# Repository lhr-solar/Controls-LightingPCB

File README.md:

# Controls-LightingPCB

Purpose: This board controls all lightings effects activated by driver controls on the inside and outside of the car.

Dimensions: 73.9140 mm by 98.8060 mm

BOM: Located under Controls-LightingPCB\BOM

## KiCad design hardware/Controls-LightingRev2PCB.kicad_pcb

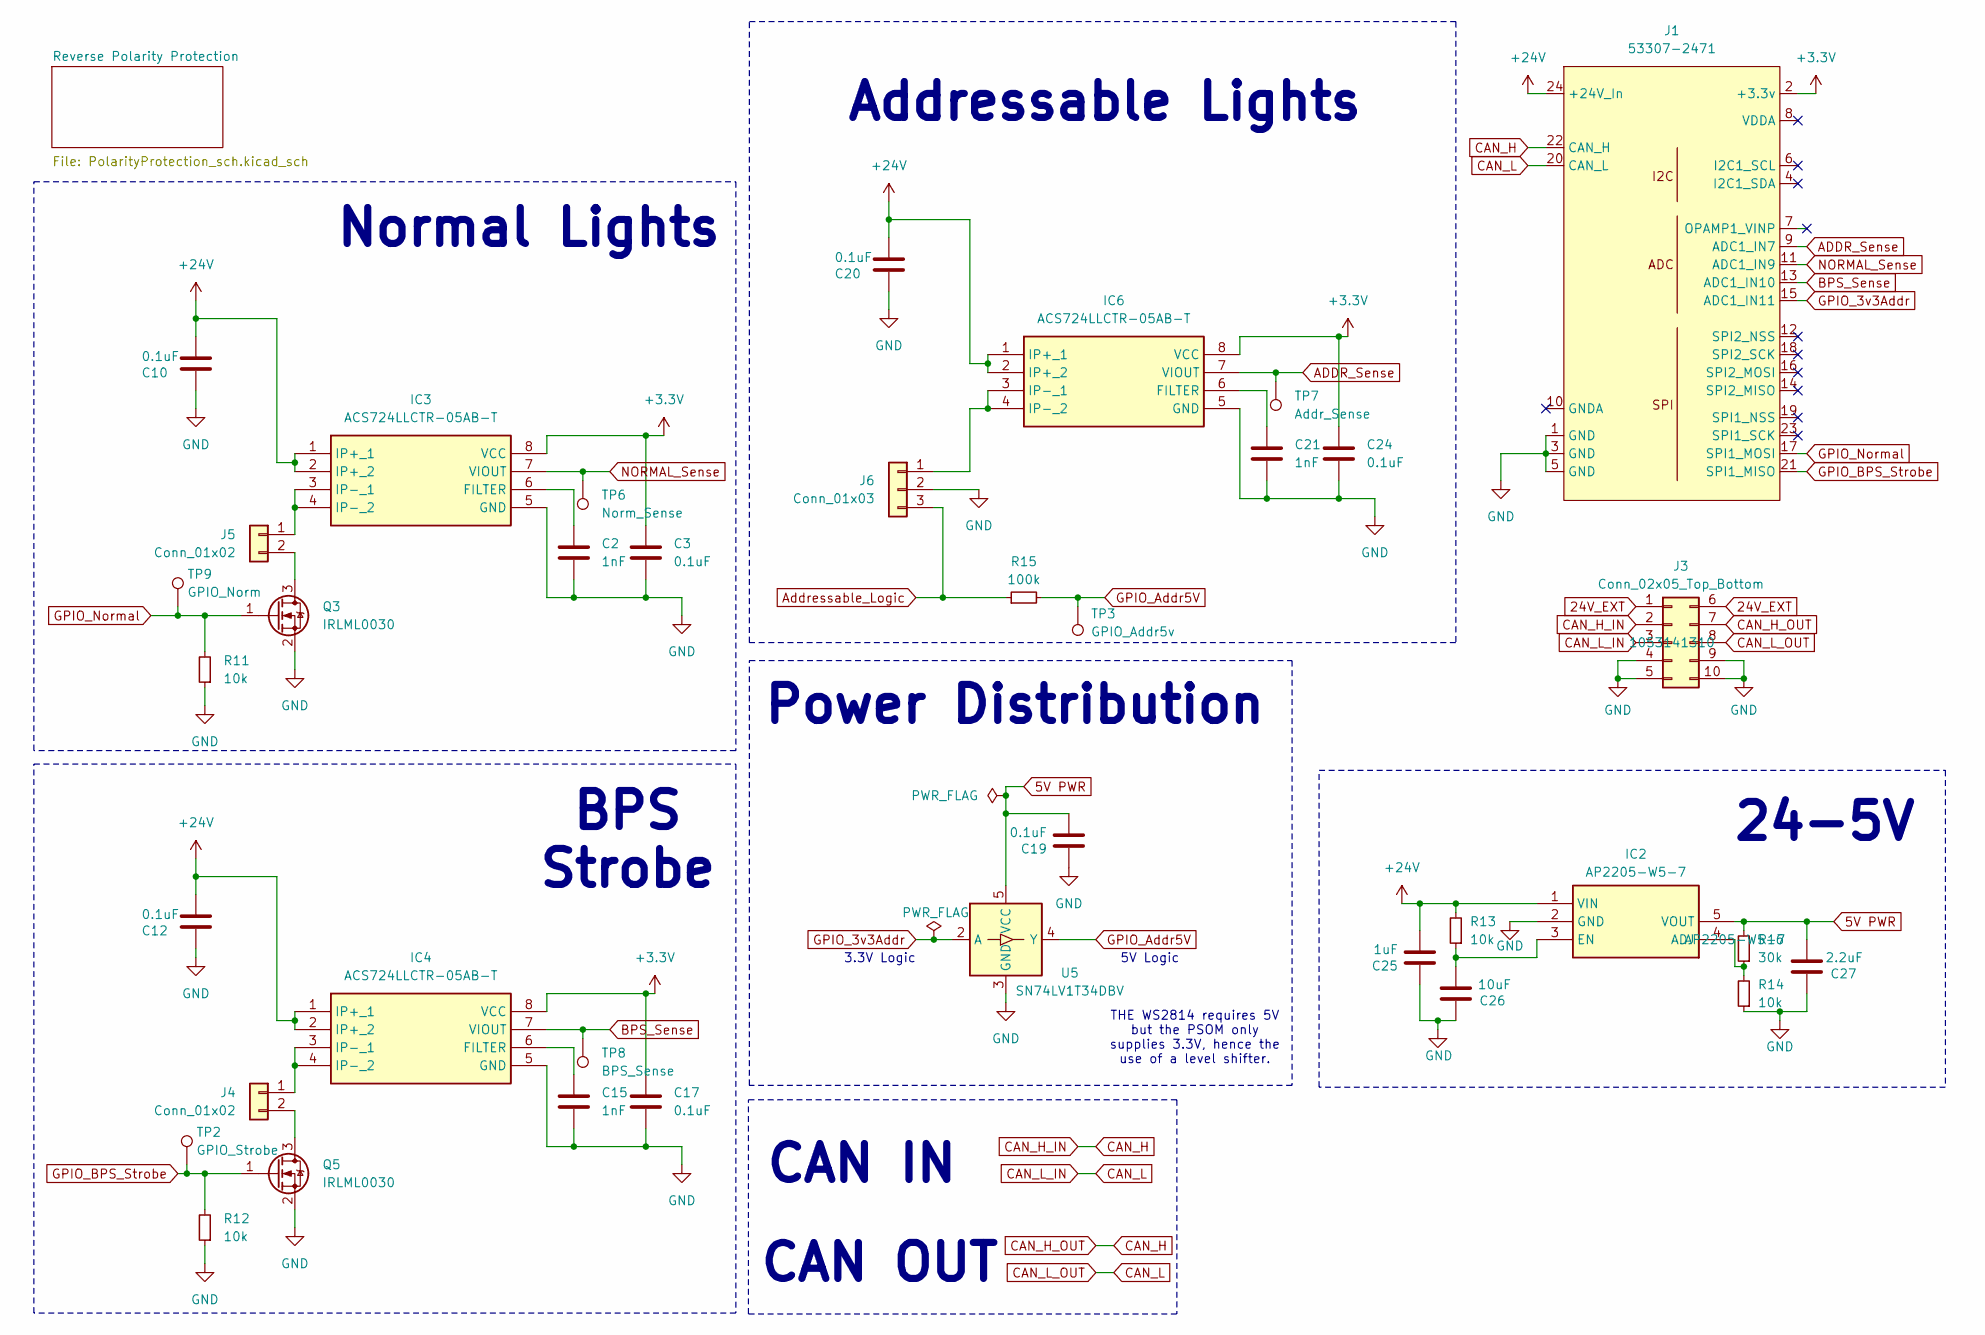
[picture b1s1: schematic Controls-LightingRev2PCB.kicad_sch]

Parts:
C2, C15, C21: 1nF; C_0603_1608Metric; LCSC P/N C1588
C3, C10, C12, C17, C19, C20, C24: 0.1uF; C_0603_1608Metric; LCSC P/N C14663
C25: 1uF; C_0603_1608Metric; LCSC P/N C15849
C26: 10uF; C_0805_2012Metric_Pad1.18x1.45mm_HandSolder; LCSC P/N C440198
C27: 2.2uF; C_0603_1608Metric; LCSC P/N C57895
IC2: AP2205-W5-7; AP2205W57; Mouser Part Number 621-AP2205-W5-7
IC3: ACS724LLCTR-05AB-T; SOIC127P600X175-8N; LCSC P/N C22392329
IC4: ACS724LLCTR-05AB-T; SOIC127P600X175-8N; Manufacturer_Part_Number ACS724LLCTR-05AB-T; LCSC P/N C22392329
IC6: ACS724LLCTR-05AB-T; SOIC127P600X175-8N; Mouser Part Number ACS724LLCTR-05AB-T
J1: 53307-2471; PeripheralSOM
J3: Conn_02x05_Top_Bottom; Molex_Nano-Fit_105314-xx10_2x05_P2.50mm_Horizontal
J4, J5: Conn_01x02; 105313-2102
J6: Conn_01x03; 105313-1103
Q3, Q5: IRLML0030; SOT-23; LCSC P/N C67272
R11, R12, R13, R14: 10k; R_0603_1608Metric; LCSC P/N C25804
R15: 100k; R_0603_1608Metric; LCSC P/N C25803
R16: 30k; R_0603_1608Metric; LCSC P/N C18681
TP2: GPIO_Strobe; TestPoint_Keystone_5005-5009_Compact
TP3: GPIO_Addr5v; TestPoint_Keystone_5005-5009_Compact
TP6: Norm_Sense; TestPoint_Keystone_5005-5009_Compact
TP7: Addr_Sense; TestPoint_Keystone_5005-5009_Compact
TP8: BPS_Sense; TestPoint_Keystone_5005-5009_Compact
TP9: GPIO_Norm; TestPoint_Keystone_5005-5009_Compact
U5: SN74LV1T34DBV; SOT-23-5; LCSC P/N C47117565

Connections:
5V PWR: C19.2, C27.2, IC2.5 (VOUT), R16.2, U5.5 (VCC)
24V_EXT: J3.1, J3.6; also elsewhere on the board
+3.3V: C3.1, C17.1, C24.1, IC3.8 (VCC), IC4.8 (VCC), IC6.8 (VCC), J1.2 (+3.3v)
+24V: C10.2, C12.2, C20.2, C25.2, IC2.1 (VIN), IC3.1 (IP+_1), IC3.2 (IP+_2), IC4.1 (IP+_1), IC4.2 (IP+_2), IC6.1 (IP+_1), IC6.2 (IP+_2), J1.24 (+24V_In), R13.2; also elsewhere on the board
ADDR_Sense: IC6.7 (VIOUT), J1.9 (ADC1_IN7), TP7.1
Addressable_Logic: J6.3, R15.1
BPS_Sense: IC4.7 (VIOUT), J1.13 (ADC1_IN10), TP8.1
CAN_H: J1.22 (CAN_H), J3.2, J3.7
CAN_L: J1.20 (CAN_L), J3.3, J3.8
GND: C2.2, C3.2, C10.1, C12.1, C15.2, C17.2, C19.1, C20.1, C21.2, C24.2, C25.1, C26.1, C27.1, IC2.2 (GND), IC3.5 (GND), IC4.5 (GND), IC6.5 (GND), J1.1 (GND), J1.3 (GND), J1.5 (GND), J3.4, J3.5, J3.9, J3.10, J6.2, Q3.2 (S), Q5.2 (S), R11.1, R12.1, R14.1, U5.3 (GND); also elsewhere on the board
GPIO_3v3Addr: J1.15 (ADC1_IN11), U5.2 (A)
GPIO_Addr5V: R15.2, TP3.1, U5.4 (Y)
GPIO_BPS_Strobe: J1.21 (SPI1_MISO), Q5.1 (G), R12.2, TP2.1
GPIO_Normal: J1.17 (SPI1_MOSI), Q3.1 (G), R11.2, TP9.1
NORMAL_Sense: IC3.7 (VIOUT), J1.11 (ADC1_IN9), TP6.1
unnamed: IC2.4 (ADJ), R14.2, R16.1
unnamed: C26.2, IC2.3 (EN), R13.1
unnamed: C2.1, IC3.6 (FILTER)
unnamed: IC3.3 (IP-_1), IC3.4 (IP-_2), J5.1
unnamed: C15.1, IC4.6 (FILTER)
unnamed: IC4.3 (IP-_1), IC4.4 (IP-_2), J4.1
unnamed: C21.1, IC6.6 (FILTER)
unnamed: IC6.3 (IP-_1), IC6.4 (IP-_2), J6.1
unnamed: J4.2, Q5.3 (D)
unnamed: J5.2, Q3.3 (D)

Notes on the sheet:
CAN IN
CAN OUT
THE WS2814 requires 5V but the PSOM only supplies 3.3V, hence the use of a level shifter.
24-5V
5V Logic
3.3V Logic
Normal Lights
Addressable Lights
Power Distribution
BPS Strobe

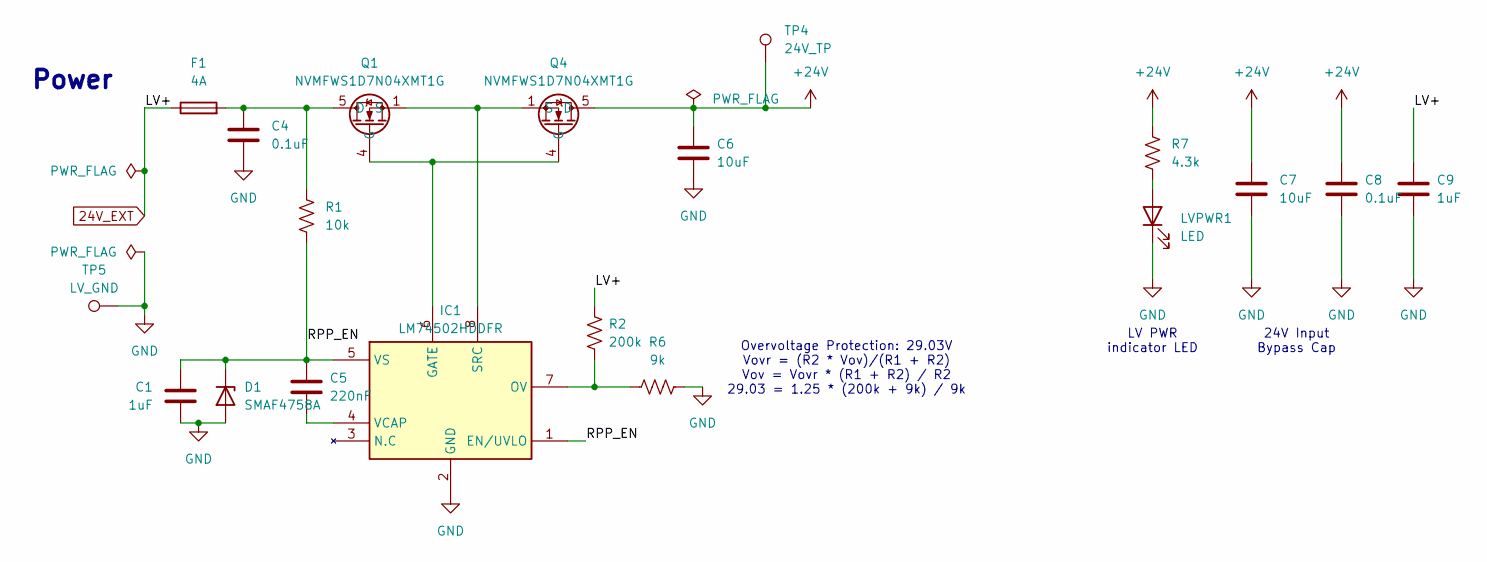
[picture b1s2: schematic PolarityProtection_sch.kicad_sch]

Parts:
C1: 1uF; C_0603_1608Metric; Mouser Part Number 963-UMK107BJ105KA-T
C4, C8: 0.1uF; C_0603_1608Metric; Mouser Part Number 963-HMK107B7104KA-T
C5: 220nF; C_0603_1608Metric; Mouser Part Number 963-MSASU168SB7224KT
C6, C7: 10uF; C_0805_2012Metric_Pad1.18x1.45mm_HandSolder; Mouser Part Number 81-GRM21BR61H106KE3K
C9: 1uF; C_0603_1608Metric; Mouser Part Number 963-HMK107B7104KA-T
D1: SMAF4758A; SODFL5026X125N
F1: 4A; FUSE_3568; Mouser P/N 534-3568
IC1: LM74502HDDFR; SOT65P280X110-8N; Mouser Part Number 595-LM74502HDDFR
LVPWR1: LED; LED_0603_1608Metric_Pad1.05x0.95mm_HandSolder; LCSC P/N C7371904
Q1, Q4: NVMFWS1D7N04XMT1G; NVMFWS3D0P04M8LT1G; LCSC P/N C133142
R1: 10k; R_0603_1608Metric; Mouser Part Number 71-CRCW060310K0FKEI
R2: 200k; R_0603_1608Metric; Mouser Part Number 594-MCT06030C2003FP5
R6: 9k; R_0603_1608Metric; Mouser Part Number 594-MCT06030C9091FP5
R7: 4.3k; R_0603_1608Metric; Mouser Part Number 71-CRCW0603-4.3K-E3
TP4: 24V_TP; TestPoint_Keystone_5005-5009_Compact
TP5: LV_GND; TestPoint_Keystone_5005-5009_Compact

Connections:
24V_EXT: C9.1, F1.1, R2.1; also elsewhere on the board
+24V: C6.1, C7.1, C8.1, Q4.5 (D), Q4.6 (D), Q4.7 (D), Q4.8 (D), Q4.9 (D), R7.1, TP4.1; also elsewhere on the board
/Reverse Polarity Protection/RPP_EN: C1.2, C5.1, D1.1 (K), IC1.1 (EN/UVLO), IC1.5 (VS), R1.2
GND: C1.1, C4.2, C6.2, C7.2, C8.2, C9.2, D1.2 (A), IC1.2 (GND), LVPWR1.1 (K), R6.2, TP5.1; also elsewhere on the board
unnamed: C4.1, F1.2, Q1.5 (D), Q1.6 (D), Q1.7 (D), Q1.8 (D), Q1.9 (D), R1.1
unnamed: IC1.6 (GATE), Q1.4 (G), Q4.4 (G)
unnamed: IC1.7 (OV), R2.2, R6.1
unnamed: IC1.8 (SRC), Q1.1 (S), Q1.2 (S), Q1.3 (S), Q4.1 (S), Q4.2 (S), Q4.3 (S)
unnamed: C5.2, IC1.4 (VCAP)
unnamed: LVPWR1.2 (A), R7.2

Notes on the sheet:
Overvoltage Protection: 29.03V Vovr = (R2 * Vov)/(R1 + R2) Vov = Vovr * (R1 + R2) / R2 29.03 = 1.25 * (200k + 9k) / 9k
24V Input Bypass Cap
LV PWR indicator LED
Power

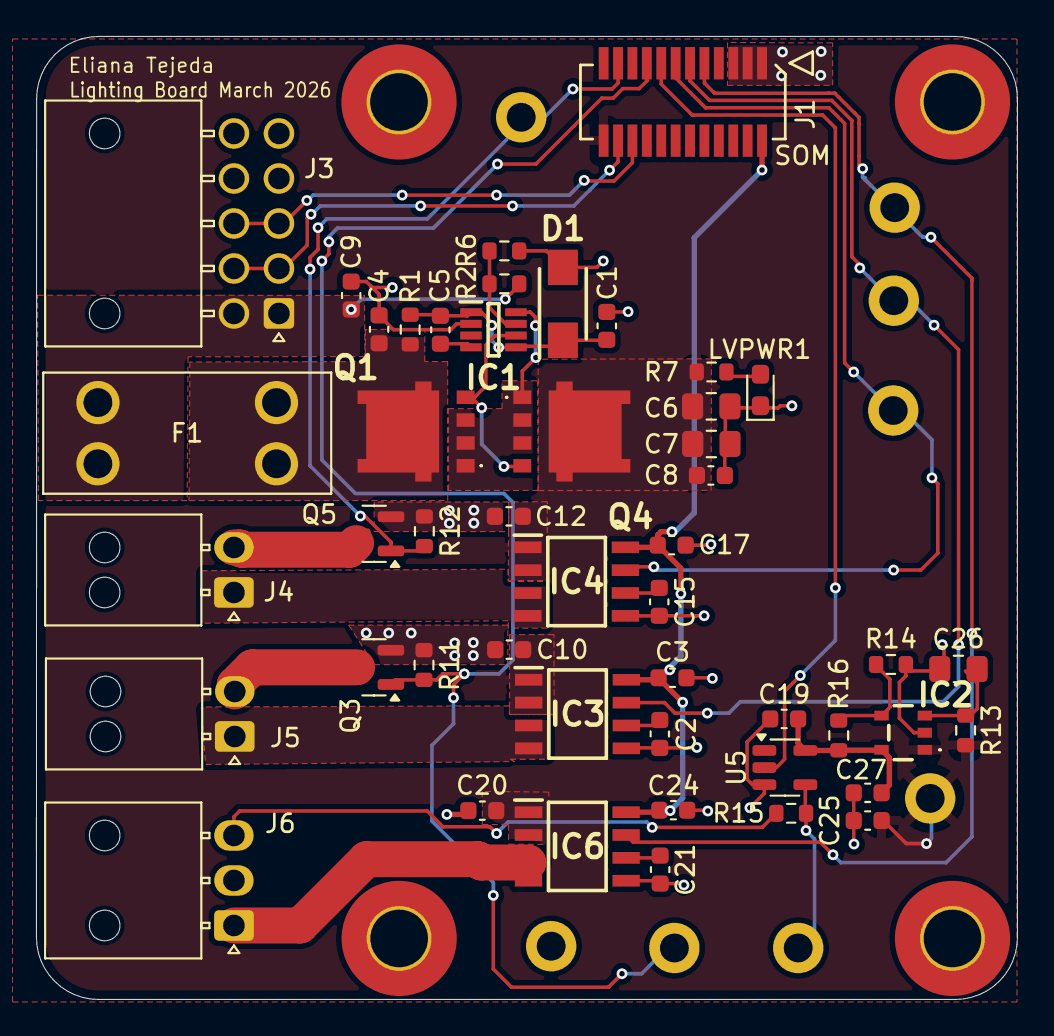
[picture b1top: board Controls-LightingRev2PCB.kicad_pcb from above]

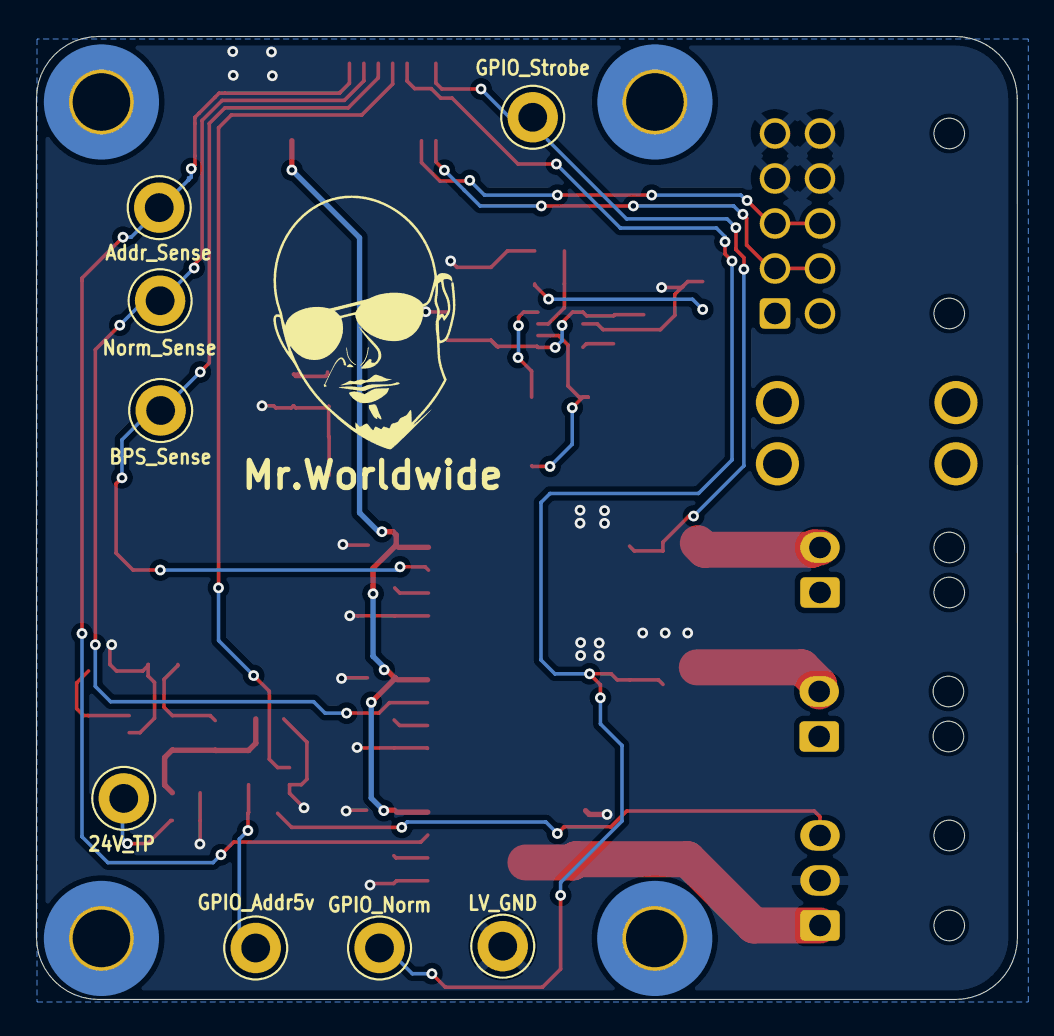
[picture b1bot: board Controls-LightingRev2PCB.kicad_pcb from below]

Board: 2 copper layers, 54.5 x 53.5 mm, 57 parts (9 on the bottom side), 32 nets.

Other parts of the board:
Mr.Worldwide: LOGO

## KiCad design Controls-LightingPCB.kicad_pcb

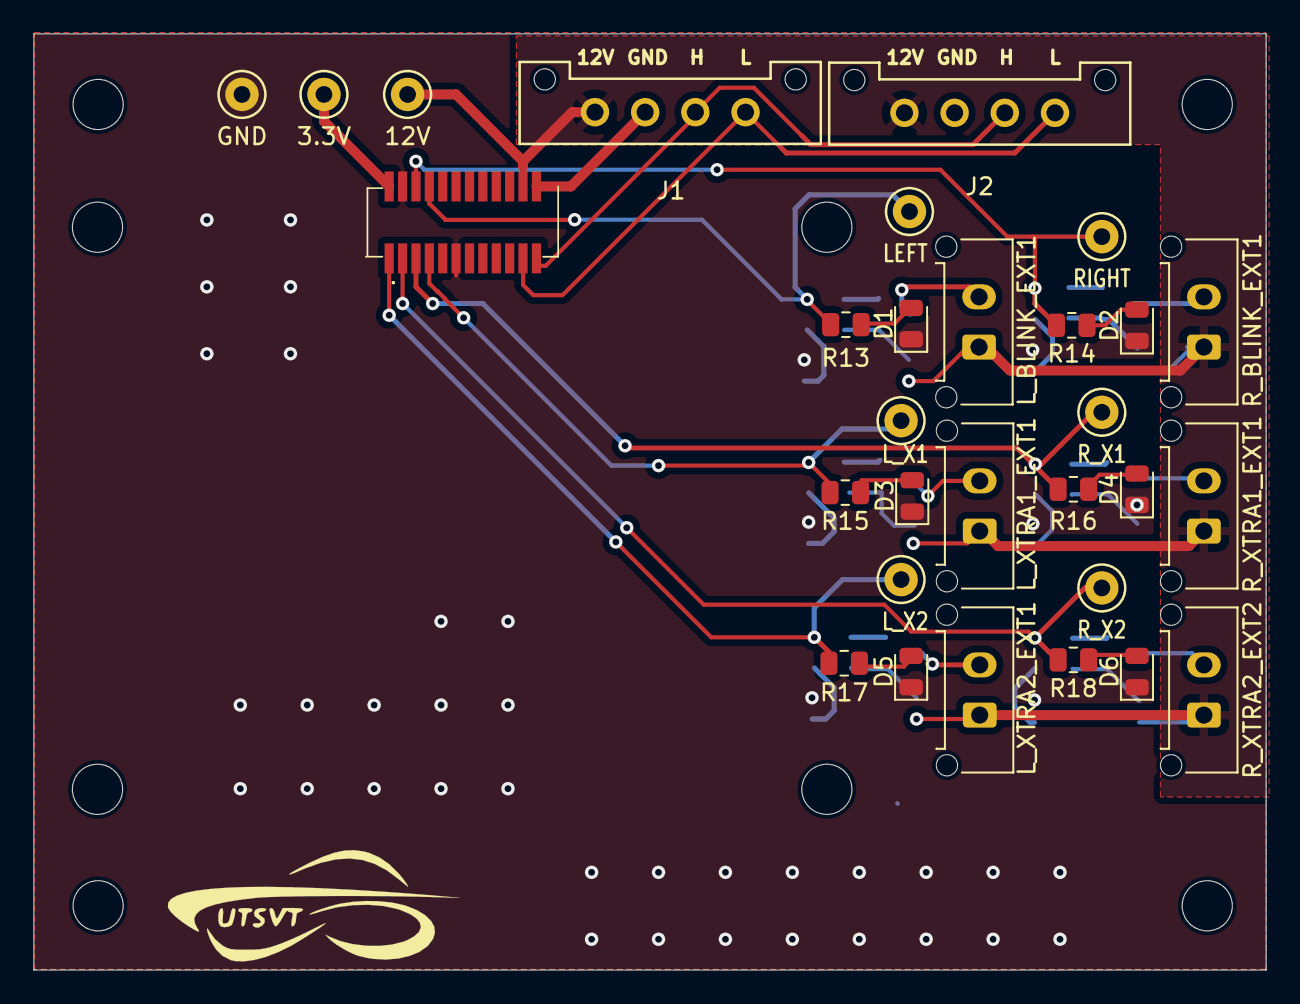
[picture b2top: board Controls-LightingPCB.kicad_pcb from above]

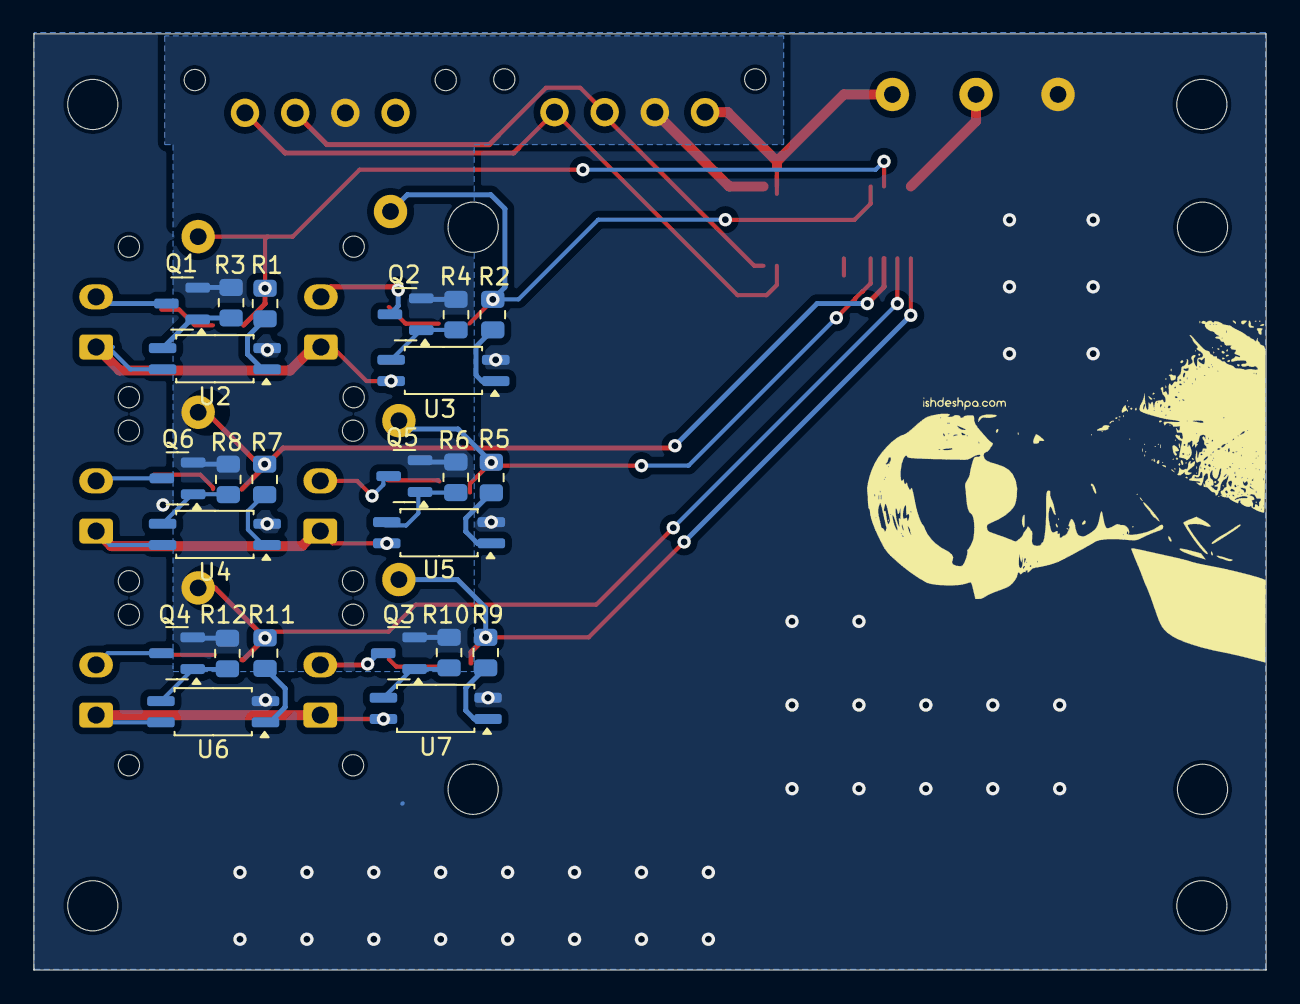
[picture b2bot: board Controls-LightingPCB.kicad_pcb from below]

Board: 2 copper layers, 73.7 x 56.0 mm, 60 parts (25 on the bottom side), 36 nets.

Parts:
3.3V: 3.3V; TestPoint_Keystone_5000-5004_Miniature
12V: 12V; TestPoint_Keystone_5000-5004_Miniature
D1: Left; LED_0805_2012Metric
D2: Right; LED_0805_2012Metric
D3: Left X1; LED_0805_2012Metric
D4: Right X1; LED_0805_2012Metric
D5: Left X2; LED_0805_2012Metric
D6: Right X2; LED_0805_2012Metric
GND: GND; TestPoint_Keystone_5000-5004_Miniature
H1, H2, H3, H4: MountingHole; MountingHole_3mm
J1, J2: PeripheralCANConnector; Molex_MicroFit3.0_1x4xP3.00mm_PolarizingPeg_Vertical
LEFT: LEFT_BLINK; TestPoint_Keystone_5000-5004_Miniature
LOGO1: Dr. Hallock Logo; Hallock_Image_Small
LOGO2: UTSVT Logo; UTSVT_Logo_Symbol
L_BLINK_EXT1: EXTERNAL_LEFTBLINK; Molex_Micro-Fit_3.0_43650-0215_1x02_P3.00mm_Vertical
L_X1: L_XTRA1_ON; TestPoint_Keystone_5000-5004_Miniature
L_X2: L_XTRA2_ON; TestPoint_Keystone_5000-5004_Miniature
L_XTRA1_EXT1, L_XTRA2_EXT1: EXTERNAL_LEFTBLINK; Molex_Micro-Fit_3.0_43650-0215_1x02_P3.00mm_Vertical
Q1, Q2, Q3, Q4, Q5, Q6: IRLML0030; SOT-23
R1, R2, R5, R7, R9, R11, R13, R14, R15, R16, R17, R18: 1k; R_0805_2012Metric
R3, R4, R6, R8, R10, R12: 100k; R_0805_2012Metric
RIGHT: RIGHT_BLINK; TestPoint_Keystone_5000-5004_Miniature
R_BLINK_EXT1: EXTERNAL_RIGHTBLINK; Molex_Micro-Fit_3.0_43650-0215_1x02_P3.00mm_Vertical
R_X1: R_XTRA1_ON; TestPoint_Keystone_5000-5004_Miniature
R_X2: R_XTRA2_ON; TestPoint_Keystone_5000-5004_Miniature
R_XTRA1_EXT1, R_XTRA2_EXT2: EXTERNAL_RIGHTBLINK; Molex_Micro-Fit_3.0_43650-0215_1x02_P3.00mm_Vertical
U1: PeripheralSOM
U2, U3, U4, U5, U6, U7: EL3H7; SSOP-4_4.4x2.6mm_P1.27mm

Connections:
+3.3V: 3.3V.1, U1.2 (+3.3V)
+12V: 12V.1, J1.1 (12V), J2.1 (12V), L_BLINK_EXT1.1, L_XTRA1_EXT1.1, L_XTRA2_EXT1.1, R_BLINK_EXT1.1, R_XTRA1_EXT1.1, R_XTRA2_EXT2.1, U1.22 (+12V_In), U2.4, U3.4, U4.4, U5.4, U6.4, U7.4
/LEFT_BLINK: LEFT.1, R2.1, R13.1, U1.8 (I2C2_SCL)
/L_XTRA1_ON: L_X1.1, R5.1, R15.1, U1.7 (SPI2_NSS)
/L_XTRA2_ON: L_X2.1, R9.1, R17.1, U1.1 (SPI2_MOSI)
/RIGHT_BLINK: R1.1, R14.1, RIGHT.1, U1.6 (I2C2_SDA)
/R_XTRA1_ON: R7.1, R16.1, R_X1.1, U1.5 (SPI2_SCK)
/R_XTRA2_ON: R11.1, R18.1, R_X2.1, U1.3 (SPI2_MISO)
GND: D1.1 (K), D2.1 (K), D3.1 (K), D4.1 (K), D5.1 (K), D6.1 (K), GND.1, U1.4 (GND), U1.11 (GND), U2.2, U3.2, U4.2, U5.2, U6.2, U7.2
GNDPWR: J1.2 (GNDPWR), J2.2 (GNDPWR), Q1.2 (S), Q2.2 (S), Q3.2 (S), Q4.2 (S), Q5.2 (S), Q6.2 (S), R3.1, R4.2, R6.2, R8.2, R10.2, R12.2, U1.24 (GNDPWR)
unnamed: D1.2 (A), R13.2
unnamed: D2.2 (A), R14.2
unnamed: D3.2 (A), R15.2
unnamed: D4.2 (A), R16.2
unnamed: D5.2 (A), R17.2
unnamed: D6.2 (A), R18.2
unnamed: J1.3 (CAN_H), J2.3 (CAN_H), U1.23 (CAN_H)
unnamed: J1.4 (CAN_L), J2.4 (CAN_L), U1.21 (CAN_L)
unnamed: L_BLINK_EXT1.2, Q2.3 (D)
unnamed: L_XTRA1_EXT1.2, Q5.3 (D)
unnamed: L_XTRA2_EXT1.2, Q3.3 (D)
unnamed: Q1.3 (D), R_BLINK_EXT1.2
unnamed: Q1.1 (G), R3.2, U2.3
unnamed: Q2.1 (G), R4.1, U3.3
unnamed: Q3.1 (G), R10.1, U7.3
unnamed: Q4.3 (D), R_XTRA2_EXT2.2
unnamed: Q4.1 (G), R12.1, U6.3
unnamed: Q5.1 (G), R6.1, U5.3
unnamed: Q6.3 (D), R_XTRA1_EXT1.2
unnamed: Q6.1 (G), R8.1, U4.3
unnamed: R1.2, U2.1
unnamed: R2.2, U3.1
unnamed: R5.2, U5.1
unnamed: R7.2, U4.1
unnamed: R9.2, U7.1
unnamed: R11.2, U6.1

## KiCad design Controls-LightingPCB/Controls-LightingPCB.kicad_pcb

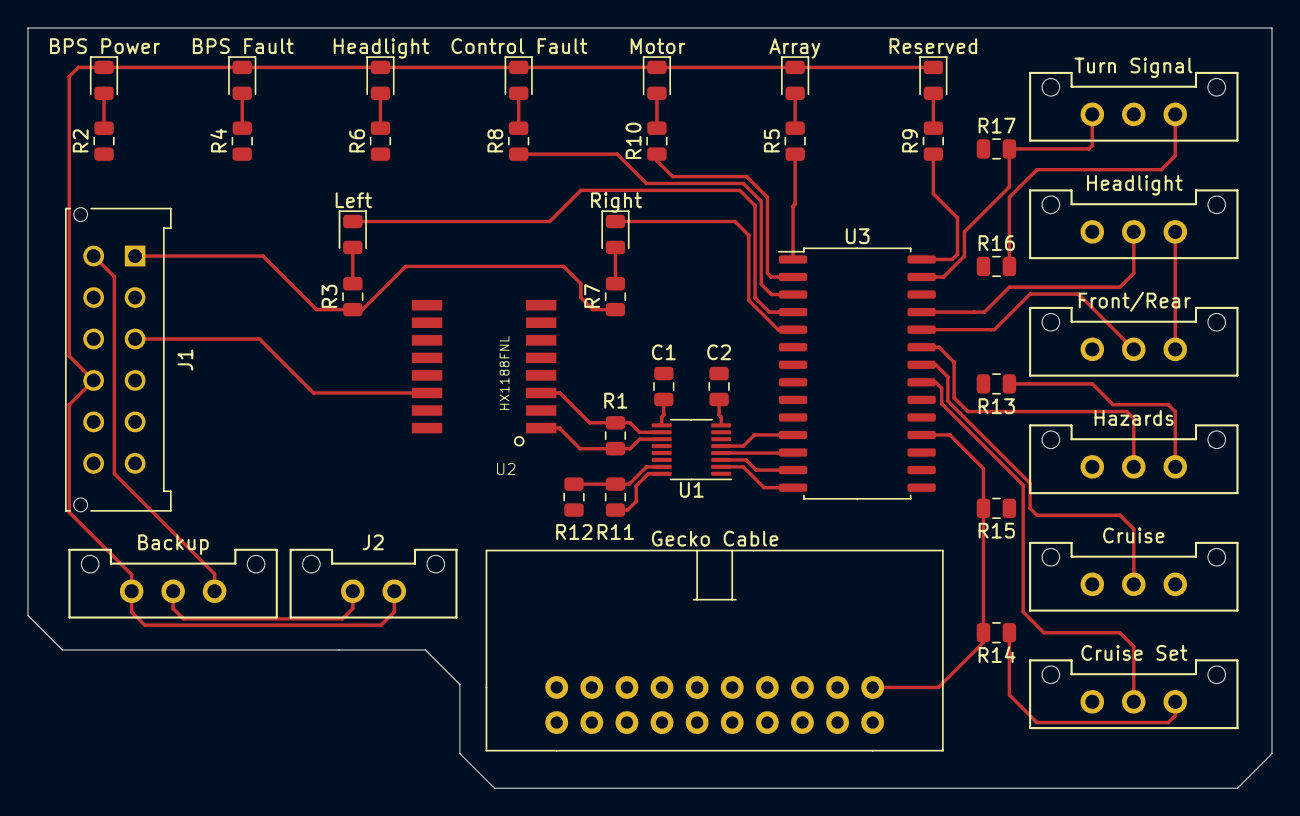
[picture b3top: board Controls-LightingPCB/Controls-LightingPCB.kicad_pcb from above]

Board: 2 copper layers, 90.0 x 55.0 mm, 41 parts (0 on the bottom side), 45 nets.

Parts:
Array: A_CNCTR; D_0805_2012Metric
BPS Fault: BPS_FAULT; D_0805_2012Metric
BPS Power: BPS_PWR; D_0805_2012Metric
Backup: BACKUP_SW; Molex_MicroFit3.0_1x3xP3.00mm_PolarizingPeg_Vertical
C1, C2: 0.1u; C_0805_2012Metric
Control Fault: CTRL_FAULT; D_0805_2012Metric
Cruise: CRUISE; Molex_MicroFit3.0_1x3xP3.00mm_PolarizingPeg_Vertical
Cruise Set: CRUISE_SET; Molex_MicroFit3.0_1x3xP3.00mm_PolarizingPeg_Vertical
Front/Rear: F/R_SW; Molex_MicroFit3.0_1x3xP3.00mm_PolarizingPeg_Vertical
Gecko Cable: Gecko_Cable; ribbon_cable_right_2x10
Hazards: HAZARD; Molex_MicroFit3.0_1x3xP3.00mm_PolarizingPeg_Vertical
Headlight: HEADLIGHT_SW; Molex_MicroFit3.0_1x3xP3.00mm_PolarizingPeg_Vertical
Headlight#2: Headlight_ON; D_0805_2012Metric
J1: MinionConn; Molex_MicroFit3.0_2x6xP3.00mm_PolarizingPeg_Vertical
J2: Backup; Molex_MicroFit3.0_1x2xP3.00mm_PolarizingPeg_Vertical
Left: LEFT_BLINK; D_0805_2012Metric
Motor: M_CNCTR; D_0805_2012Metric
R1: 120; R_0805_2012Metric
R2, R12: 1.2k; R_0805_2012Metric
R3, R4, R5, R6, R7, R8, R9, R10: 330R; R_0805_2012Metric
R11: 806; R_0805_2012Metric
R13, R14, R15, R16, R17: 10k; R_0805_2012Metric
Reserved: RSVD_LED; D_0805_2012Metric
Right: RIGHT_BLINK; D_0805_2012Metric
Turn Signal: TURN_SIGNAL_SW; Molex_MicroFit3.0_1x3xP3.00mm_PolarizingPeg_Vertical
U1: LTC6820; MSOP-16_3x4mm_P0.5mm
U2: HX1188FNL; HXXXX
U3: MCP23S17_SO; SOIC-28W_7.5x17.9mm_P1.27mm

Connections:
+3V3: C1.1, C2.1, Front/Rear.3, Gecko Cable.11, Headlight.3, J1.1, R3.1, R7.1, R13.2, R14.2, R15.2, R16.1, R17.1, U1.6, U1.7, U1.8, U1.9, U3.9, U3.18
+12V: Backup.3, J1.7
/ControlLEDs/A_CNCTR: R5.1, U3.1
/ControlLEDs/BPS_FAULT: R4.1, U3.7
/ControlLEDs/BPS_PWR: R2.1, U3.8
/ControlLEDs/CTRL_FAULT: R8.1, U3.3
/ControlLEDs/Headlight_ON: R6.1, U3.6
/ControlLEDs/LEFT_BLINK: Left.1, U3.4
/ControlLEDs/M_CNCTR: R10.1, U3.2
/ControlLEDs/RIGHT_BLINK: Right.1, U3.5
/ControlLEDs/RSVD_LED: R9.1, U3.28
/ControlSwitches/Backup: Backup.2, J2.1
/ControlSwitches/CRUZ_EN: Cruise.2, U3.22
/ControlSwitches/CRUZ_ST: Cruise Set.2, U3.21
/ControlSwitches/FR_SW: Front/Rear.2, U3.24
/ControlSwitches/HZD_SW: Hazards.2, U3.23
/ControlSwitches/Headlight_SW: Headlight.2, U3.25
/ControlSwitches/LEFT_SW: R16.2, Turn Signal.3, U3.26
/ControlSwitches/RIGHT_SW: R17.2, Turn Signal.1, U3.27
/IM: R1.2, U1.10, U2.3
/IP: R1.1, U1.11, U2.1
/ShiftReg/CS: U1.5, U3.11
/ShiftReg/MISO: U1.3, U3.13
/ShiftReg/MOSI: U1.2, U3.14
/ShiftReg/SCK: U1.4, U3.12
/UART-Tx: Gecko Cable.16, J1.8
/UART_Rx: Gecko Cable.17, J1.9
GND: C1.2, C2.2, Cruise.1, Cruise Set.1, Front/Rear.1, Gecko Cable.1, Hazards.1, Headlight.1, J1.4, R12.1, Turn Signal.2, U1.1, U1.12, U1.13, U1.14, U3.10, U3.15, U3.16, U3.17
GNDPWR: Array.1, BPS Fault.1, BPS Power.1, Backup.1, Control Fault.1, Headlight#2.1, J1.10, J2.2, Motor.1, Reserved.1
unnamed: BPS Power.2, R2.2
unnamed: Left.2, R3.2
unnamed: BPS Fault.2, R4.2
unnamed: Array.2, R5.2
unnamed: Headlight#2.2, R6.2
unnamed: R7.2, Right.2
unnamed: Control Fault.2, R8.2
unnamed: R9.2, Reserved.2
unnamed: Motor.2, R10.2
unnamed: J1.2, U2.16
unnamed: J1.3, U2.14
unnamed: R11.1, R12.2, U1.15
unnamed: R11.2, U1.16
unnamed: Hazards.3, R13.1
unnamed: Cruise Set.3, R14.1
unnamed: Cruise.3, R15.1

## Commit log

2020-09-19 Added UTSVT KiCad Libraries
2020-09-26 Started working on PCB layout
2020-09-26 Finished PCB layout
2020-10-03 Adds hierarchical sheets for control switches and switch register
2020-10-03 Adds QuAC
2020-10-03 Creates hierarchical sheets
2020-10-03 Added hierarchical sheets and connections
2020-10-03 Added HX1188FNL
2020-10-03 Added LTC6820
2020-10-03 Edited cap and res values
2020-10-09 Started working on PCD design, preliminary layout of components
2020-10-10 Moves files out of individual folder and updates library paths
2020-10-10 Added changes to PCB Design
2020-10-10 Updated board component labels
2020-10-17 Switched LEDs to back side and changed dimensions of board
2020-10-17 Tried to start layout of the back side
2020-10-17 Made connections on back of the board
2020-10-17 Finished vias. Isolated U2 from GND and GNDPWR.
2020-10-18 Redid some connections.
2020-10-24 Added switch labels and got through most of checklist
2020-10-24 Added mounting holes and adjusted design accordingly
2020-10-24 Fixed switch labels
2020-10-31 Deleted TODO in Switches
2020-11-14 Minor changes
2020-11-14 Changed orientation and dimensions of board.
2020-11-14 Resized PCB, changed switches to horizontal, need to organize components
2020-11-21 Changed all switch connectors to horizontal, board dimensions to 2.5in by 4.5in, and started board layout
2020-11-21 Added Regen switch, deleted RSVD LED
2020-11-22 Started placing routes, did not finish
2020-12-02 Added several tracks, fixed exclusion zone
2020-12-03 Finished connections and changed F/W switch, but hierarchial labels on schematic need to be fixed
2020-12-04 Updated schematic with changed F/W switch and BPS_PWR direct connection to MinionConn
2020-12-04 Changed minion conn
2020-12-04 Finished current updates to the board
2020-12-04 Changed Shift Regsiter labels to GPIO Expander
2020-12-05 Fixing merge issues
2020-12-05 Fixed BPS_PWR lines
2020-12-19 Changed Schematic, but not PCB layout. Updated LED resistor values
2020-12-19 Reformatted PCB layout with schematic changes
2020-12-19 Changed switches
2020-12-19 Board finished with the new changes, needs to be checked
2020-12-20 Fixes switch/button circuitry
2021-01-10 Adds gerbers
2021-01-23 3D edits
2021-01-23 Finished 3D edits
2021-10-02 Added resistor and diode
2021-10-03 Extends keepout zone
2021-10-03 Remove some ground plane underneath isoSPI signals
2021-10-04 Updates gerbers and version number
2021-10-30 Adds the gerbers
2021-10-30 Footprint edit
2021-11-13 isoSPI -> SPI change
2021-11-13 isoSPI -> SPI 2
2021-11-20 Deleted backup camera
2021-11-21 makes changes to traces(11/20/21)
2021-11-21 Reviews layout
2021-12-07 Adds gerbers and finalizes the new version
2022-05-01 Fix issue with LED
2022-05-21 Adds 60ohm resistor to MISO line
2022-08-19 added clk circuit, began removing unnecessary nets and pins
2022-08-21 finished schematic rev1
2022-08-27 redo schematic
2022-08-30 added todo
2022-09-01 added comments
2022-09-02 added brakelight
2022-09-08 added capacitors to the switches, no-pop resistors to the light ports, added ports for internal indicator lights
2022-09-08 Sid can't see comments
2022-09-10 edits
2022-09-10 Added low side mosfet, small fixes to timer circuit
2022-09-10 changed to low-side mosfet switching on IC after switching IC to +5v instead of +12v.
2022-09-12 added pull-downs for mosfets, fixed mosfet orientation, added real diodes
2022-09-12 Added a few questions and comments for design review
2022-09-12 fixed diode protection
2022-09-17 finished adding backup ports for gear selector and SW lights
2022-09-17 reverted to buttons for cruise control
2022-09-28 PCB layout #1
2022-10-03 is square now
2022-10-15 Component layout
2022-10-15 Pico-Claps connectors + traces
2022-10-22 Changes to traces/silkscreens
2022-10-22 edge cuts
2022-11-05 moved components to front, fixed traces/planes
2022-11-05 Changed to SMD mosfets
2022-11-12 updated board
2022-11-12 changes to traces and movement of test points
2022-11-19 dimensions
2022-11-19 dimensions but like fr this time
2022-12-03 Changes to track/via sizes
2022-12-03 Changes to planes
2022-12-10 First bad layout
2022-12-10 finished layout
2022-12-10 Added more stitching vias on edges of board
2022-12-12 moved traces away from tht connectors
2023-01-06 Created Gerber and Drill Files
2023-01-21 component updates
2023-01-27 fixed timer
2023-01-28 Change schematics
2023-01-29 schematic fixes and minor changes. no major part changes
2023-01-29 cleanup
2023-01-29 replace and reroute
2023-01-29 silkscreen
2023-01-29 ibom
2023-01-29 review changes
2023-01-30 strategic bombing
2023-02-02 gerbers
2023-05-22 Made several QAC changes as per new attempt to standardize PCB Design
2023-05-22 Revert "Made several QAC changes as per new attempt to standardize PCB Design"
    This reverts commit 52861749412b440a917f1d7e0c48393e05b5e681.
2023-05-22 Made additional changes as part of QAC
2023-06-13 Added Opto-Isolators to Minion Connector interfacing
2023-06-13 Added secondary schematic for Minion Connector
2023-06-19 Fixed Submodule and started Standardizing
2023-06-19 Finished Schematic
2023-08-07 Opto-Isolators now interface mosfets to avoid ground problems, also separated 12V 'power' ground and ground passed from minion connector
2023-08-23 Did layout
2023-08-23 Fixed plane and created gerbers
2023-08-23 Updated submodule
2023-08-23 Updated Pull Request Template
2023-08-26 Updated html bom
2023-09-25 Updated gerbers zip
2023-10-10 Added BOM
2023-10-10 Converted to excel sheet
2024-11-06 deleted 555 timer
2024-11-09 replaced gate driver and updated limiting resistor, added psom connector (made no connections yet)
2024-11-15 schematic complete (?)
2024-12-07 got rid of headlights and brakelights, adjusted pinout to include just two connectors to two lights
2025-01-16 added two more light connectors to board
2025-01-25 accommodated for 6 lights on one board, added test points and leds on board
2025-02-01 simplified circuit and reduced testpoints
2025-02-01 added second can connector and changed resistor values for SMD LEDs
2025-02-01 added footprints for all components
2025-02-01 changed lights resistor values and updated EL2H7 footprint
2025-02-08 small changes, debating new connectors
2025-02-27 prelim board layout
2025-02-28 updated prelim
2025-03-01 layout before connecting traces
2025-03-17 moved mounting holes inward
2025-03-19 finished wiring, only DRC error is for how close the pads are on the psom, think it can be ignored??
2025-03-20 board rewire (ongoing)
2025-03-20 continued wiring WIP
2025-03-29 completed layout
2025-03-29 small changes
2025-03-29 image change
2025-03-30 changes made to size of planes
2025-03-30 small changes for aesthetics
2025-03-31 layout fixes
2025-03-31 layout adjustments to make a more solid ground plane
2025-04-02 silkscreen fixes
2025-08-31 Initial Schematic
    Lighting Board Initial Schematic.
2025-09-04 cleaned up repo
2025-09-04 repo cleanup stuff
2025-09-05 Need 24V to 5V from PSOM PCB
2025-09-05 Need 24 to 5V from PSOM
2025-09-05 Remove old files
2025-09-12 Added reverse polarity, 5v buck, assigned shunt and feedback resistor values, and GPIO pins
2025-09-16 Switched to a current sensing IC and assigned a new shunt value according to a fixed gain of 200.
2025-09-19 Initial Schematic Review for addressble lights, normal lights, and BPS strobe.
2025-09-19 Ready for Review
2025-09-24 Add shared KiCad libraries and update .gitmodules
2025-09-24 Removed old schematic files
2025-09-24 Added 16 pin connector, fuse, and BPS strobe circuit.
2025-09-27 Review BPS strobe, additional fuse, and buck.
2025-09-27 Hopefully last schematic review
2025-10-08 New board dimensions
2025-10-08 Clean submodule KiCAD-Sharepoint
2025-10-08 Componenent Layout, I branched into MX150_Connectors however, I can't seem to find the 2x8 connector. It's probably an issue on my end but I can look into it later
2025-10-12 Routed but having issues with gnd being pretty isolated
2025-10-22 Test points added
2025-10-22 slight test point and keep out updates
2025-10-22 rounded corners + gerbers
2025-10-22 make source trace larger + fix minor clearance violations
2025-10-22 regen gerber files
2025-12-06 RevA
2025-12-06 Remove unused files
2025-12-19 Rev B initial rework
2025-12-23 Correct LDO
2026-01-05 Rev B schematic Review for correct SOM connector and new IC
2026-01-05 Rev B schematic Review with new IC
2026-01-08 Switched MX150 to 02x05 nanofet
2026-01-08 Current Layout
2026-01-09 Layout
2026-01-09 Layout 53.5
2026-01-09 layout recommendations
2026-01-09 Layout Review
2026-01-10 Some routing
2026-01-11 Ready for Layout Review
2026-01-12 All review requests escept LDO addressed
2026-01-12 Changes from Review Request
2026-01-12 Layout complete and ready for review
2026-01-13 Hopefully Final Review
2026-01-13 Adjusted test points for better gnd and power connection
2026-01-13 Layout with 0 DRS and polarity errors
2026-01-14 Bom and Final Layout
2026-01-14 Bom + Layout
2026-03-07 firmware
2026-03-08 poop
2026-03-15 add JLCPCB assembly files
2026-03-15 move connectors a lil bit
